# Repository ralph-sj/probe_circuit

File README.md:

# README
## RAS-J 12/01/2017

## Introduction
Here the design of a POF sensor is presented for the remote monitoring of a distillation column for use in undergraduate labs within Chemical Engineering.

## Hardware layout
The circuit is based around the LT1920 instrumentation amplifier which is used to amplify the signal from a photodiode with an incorporated trans-impedance amplifier.  

- Power input: this is supplied from a 12V supply connected to a 2.5mm jack on the front panel 
- LED power output: voltage for the LED's is connected to 2 banana plugs (red and black) on the front panel.
- Vsig output: this is the output signal and is connected by a BNC plug
- Vpd: the input from the photodiode.  This is at present connected via a 2.5mm audio jack but this can be replaced with a BNC connector

Resistors are used to set the levels for the offset voltage and the gain of the amplifier.  Switches are used to switch between variable resistors and fixed value resistors.  This is to enable the optimum level of both to be found and then set for future use.

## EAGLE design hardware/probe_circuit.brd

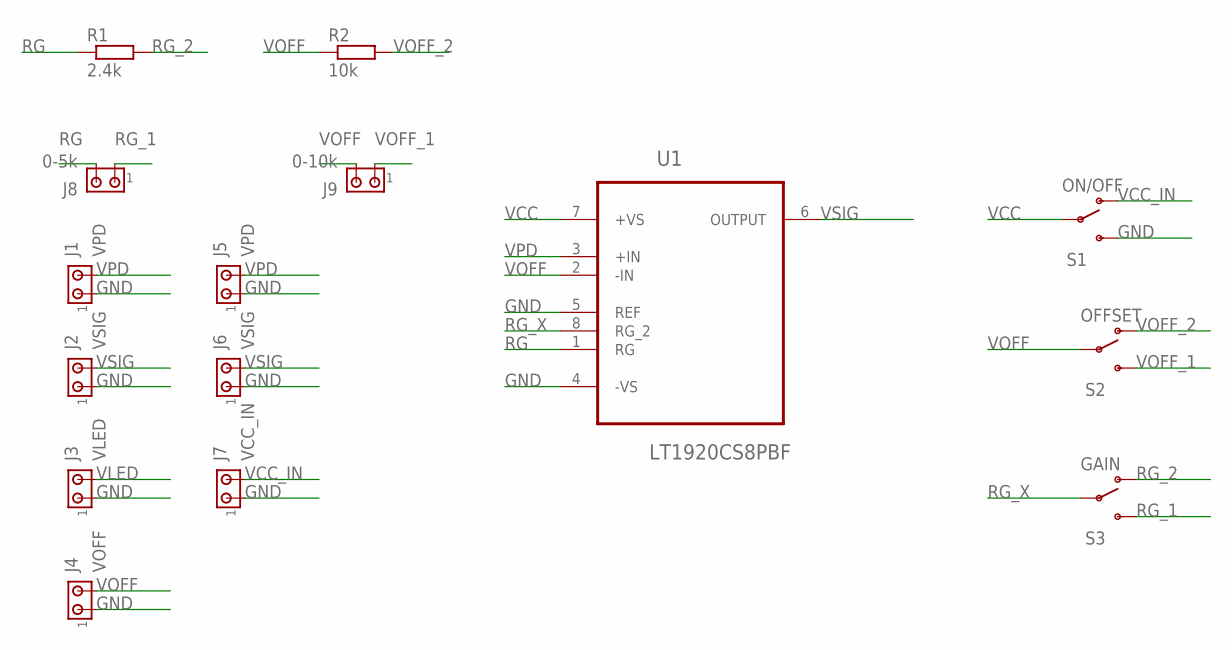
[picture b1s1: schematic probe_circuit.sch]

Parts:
J1, J5: VPD; 10X02MTA
J2, J6: VSIG; 10X02MTA
J3: VLED; 10X02MTA
J4: VOFF; 10X02MTA
J7: VCC_IN; 10X02MTA
J8: 0-5k; 10X02MTA
J9: 0-10k; 10X02MTA
R1: 2.4k; 0204/7
R2: 10k; 0204/7
S1: ON/OFF; SWITCH-SPDT
S2: OFFSET; SWITCH-SPDT
S3: GAIN; SWITCH-SPDT
U1: LT1920CS8PBF; SOIC127P600X175-8N

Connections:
GND: J1.1, J2.1, J3.1, J4.1, J5.1, J6.1, J7.1, S1.3 (S), U1.4 (-VS), U1.5 (REF)
RG: J8.2, R1.1, U1.1 (RG)
RG_1: J8.1, S3.3 (S)
RG_2: R1.2, S3.1 (O)
RG_X: S3.2, U1.8 (RG_2)
VCC: S1.2, U1.7 (+VS); also elsewhere on the board
VCC_IN: J7.2, S1.1 (O)
VLED: J3.2; also elsewhere on the board
VOFF: J4.2, J9.2, R2.1, S2.2, U1.2 (-IN)
VOFF_1: J9.1, S2.3 (S)
VOFF_2: R2.2, S2.1 (O)
VPD: J1.2, J5.2, U1.3 (+IN)
VSIG: J2.2, J6.2, U1.6 (OUTPUT)

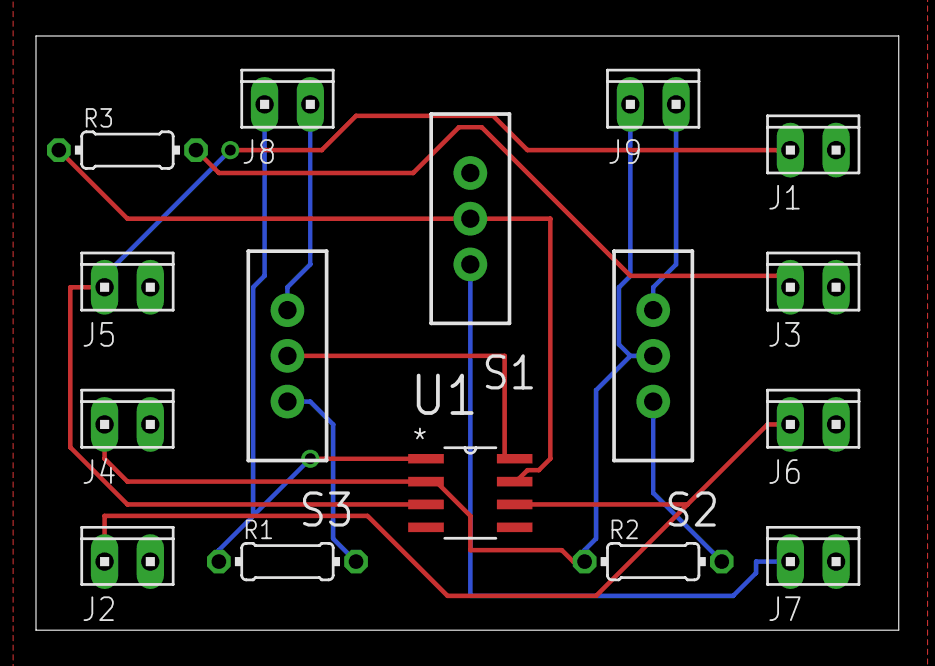
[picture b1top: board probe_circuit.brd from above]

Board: 2 copper layers, 47.9 x 33.0 mm, 16 parts (0 on the bottom side), 13 nets.

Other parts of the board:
R3: R_LED; 0204/7

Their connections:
VCC: R3.1; also elsewhere on the board
VLED: R3.2; also elsewhere on the board

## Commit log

2016-10-27 :lollipop: Added .gitattributes & .gitignore files
2016-10-27 Added schematic
2016-10-27 Added components to board
    - added LT1920 and resistor to board
    - generated PCB
2016-10-28 Parts spreadsheet added
    - plug parts (potential) logged to file
2016-10-28 update parts list
    - added audio plug/jack for signal connector
2016-10-31 - updated parts list
2016-10-31 added gain calculator
2016-10-31 - updated PCB
    - added example switches, connector points and resistors to the board
2016-10-31 update parts list
2016-12-19 AddedInst. Op. Amp. to parts
2016-12-19 Added connectors for variable resisotrs and conmpressed board.
2016-12-19 updated board polygon areas and printed pdf view pf board
2016-12-20 Connected VLED to VCC via resistor. Amended polygon area.
2016-12-20 Printed brd and sch files to pdf
2017-01-17 added circuit and physical outline sketches
2017-01-17 added README
2017-01-17 updated box design svg and parts list

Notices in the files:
parts and their libraries:
SparkFun-Electromechanical: Licensing: Creative Commons ShareAlike 4.0 International - https://creativecommons.org/licenses/by-sa/4.0
